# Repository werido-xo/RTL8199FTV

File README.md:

- 👋 Hi, I’m @werido-xo, in china.
- 👀 I’m interested in embeded linux
- 🌱 I’m currently learning data structure and algri
- 💞️ I’m looking to collaborate on ...
- 📫 How to reach me ...

<!---
werido-xo/werido-xo is a ✨ special ✨ repository because its `README.md` (this file) appears on your GitHub profile.
You can click the Preview link to take a look at your changes.
--->

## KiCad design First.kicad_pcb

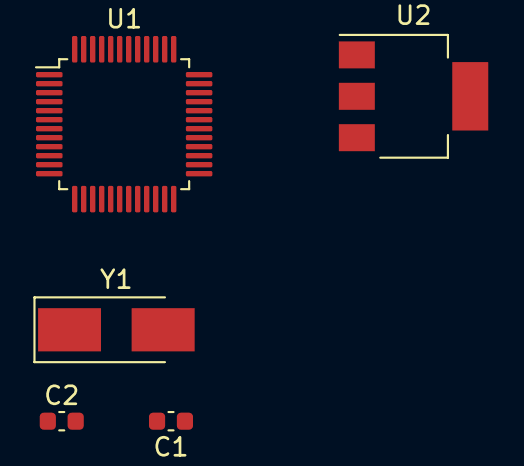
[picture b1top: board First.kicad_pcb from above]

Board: 2 copper layers, 5 parts (0 on the bottom side), 4 nets, no tracks yet.

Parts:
C1, C2: C; C_0603_1608Metric
U1: STM32F103C8Tx; LQFP-48_7x7mm_P0.5mm
U2: AMS1117-3.3; SOT-223-3_TabPin2
Y1: Crystal; Crystal_SMD_5032-2Pin_5.0x3.2mm_HandSoldering

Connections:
/OSC-IN: C1.2, Y1.2
/OSC-OUT: C2.2, Y1.1
unnamed: C1.1, C2.1
unnamed: U1.23 (VSS), U1.35 (VSS), U1.47 (VSS)

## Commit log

2023-02-25 STM32 MiniBoard Project Initialize
